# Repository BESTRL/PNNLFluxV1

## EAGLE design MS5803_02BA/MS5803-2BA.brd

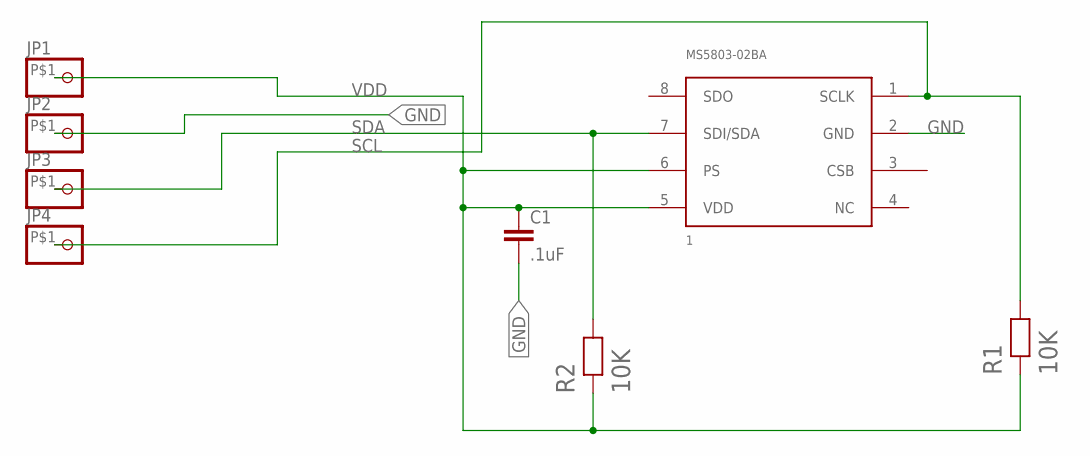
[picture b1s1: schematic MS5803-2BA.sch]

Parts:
C1: .1uF; C0805
JP1, JP2, JP3, JP4: PINHD-1X11X01SM; 1X01SM
MS5803-02BA: 1; MS5803-02BA
R1, R2: 10K; 2012(0805)RESISTOR

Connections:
GND: C1.2, JP2.P$1, MS5803-02BA.2 (GND)
SCL: JP4.P$1, MS5803-02BA.1 (SCLK), R1.2
SDA: JP3.P$1, MS5803-02BA.7 (SDI/SDA), R2.2
VDD: C1.1, JP1.P$1, MS5803-02BA.5 (VDD), MS5803-02BA.6 (PS), R1.1, R2.1

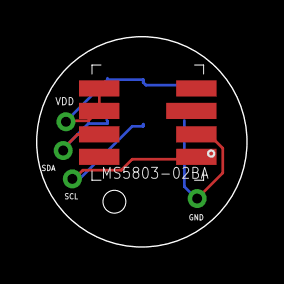
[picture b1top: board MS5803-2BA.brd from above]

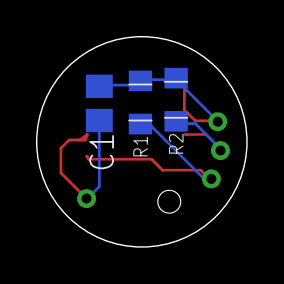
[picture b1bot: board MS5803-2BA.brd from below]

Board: 2 copper layers, 11.7 x 11.7 mm, 8 parts (3 on the bottom side), 4 nets.

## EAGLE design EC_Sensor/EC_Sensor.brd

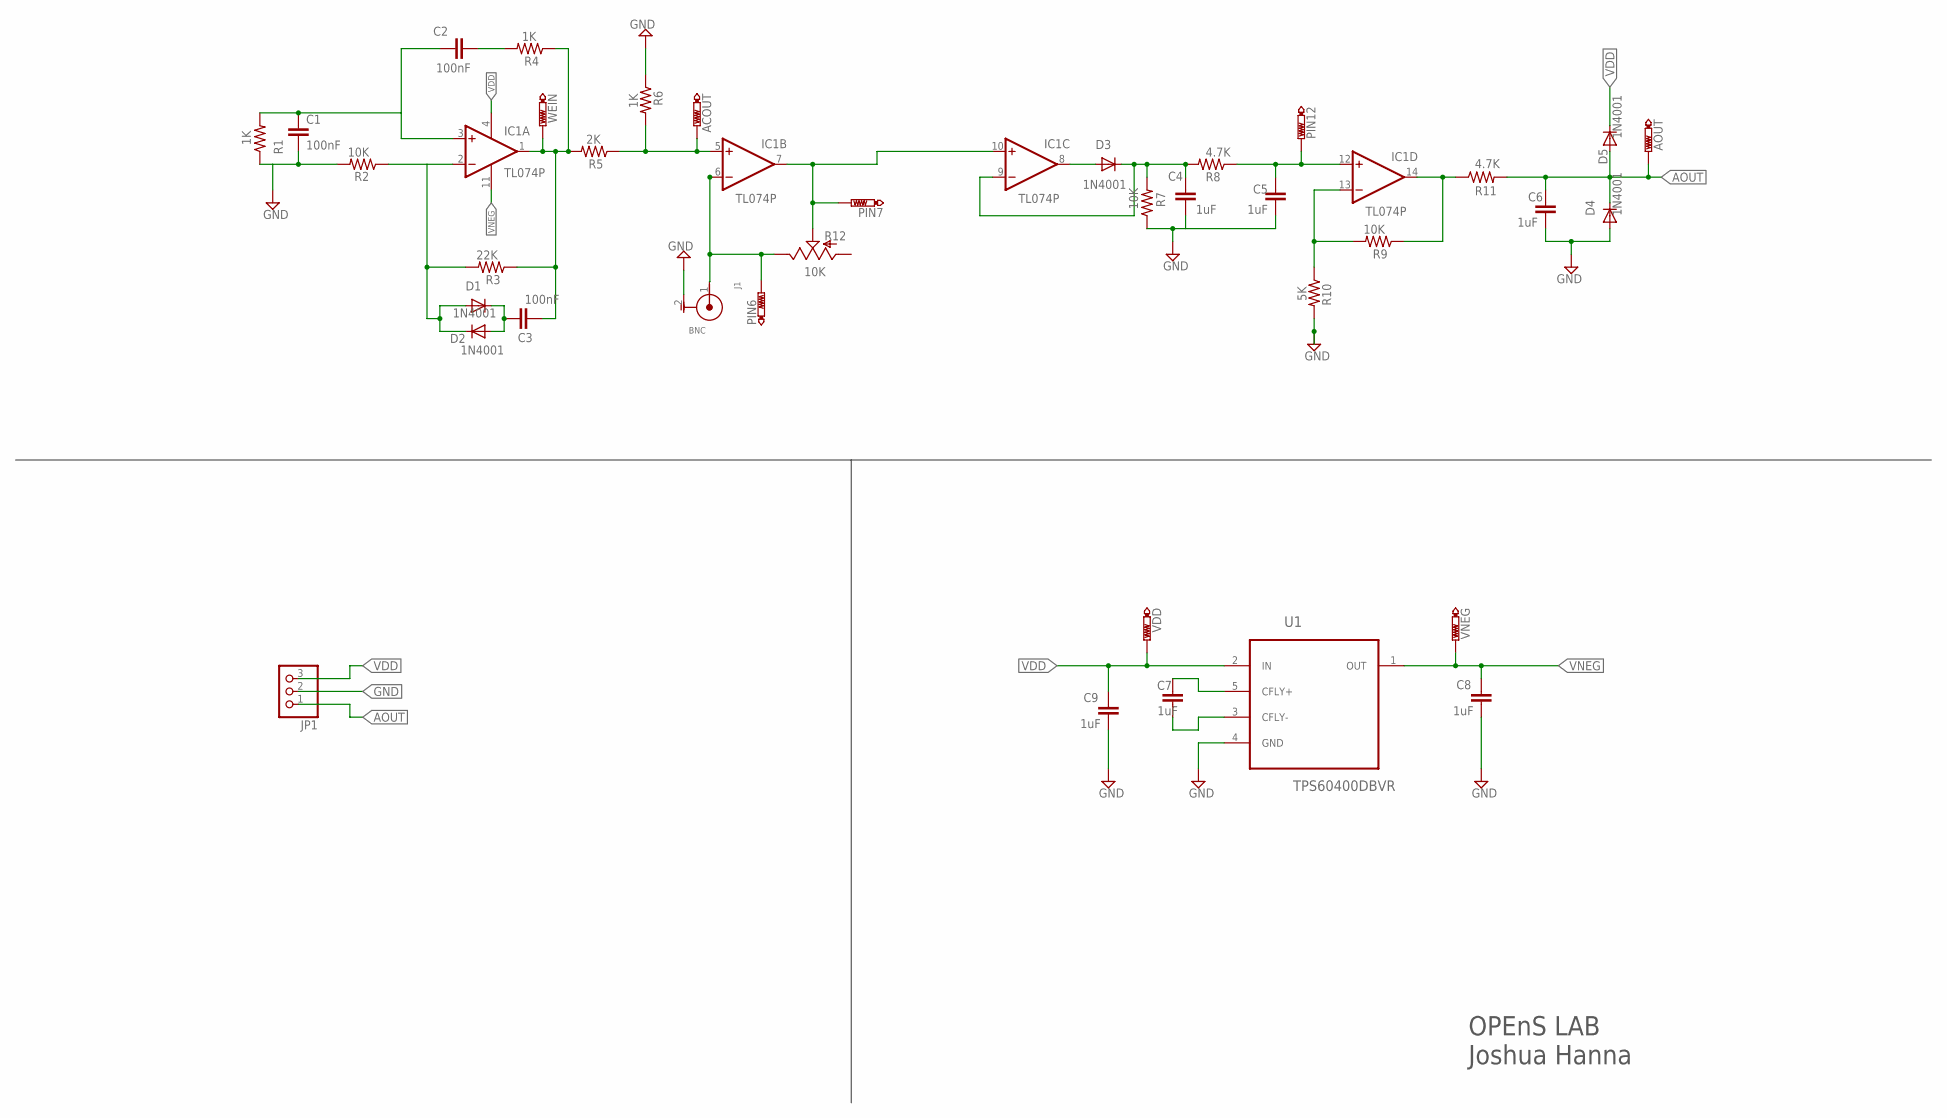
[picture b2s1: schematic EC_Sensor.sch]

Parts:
ACOUT: PTR1PAD1-13; P1-13
AOUT: PTR1PAD1-13; P1-13
C1, C2, C3: 100nF; C1206
C4, C5, C6, C7, C8, C9: 1uF; C1206
D1, D2, D3, D4, D5: 1N4001; D-5
IC1: TL074P; DIL14
J1: BNC; TE_227161-1
JP1: PINHD-1X3; 1X03
PIN6, PIN7, PIN12: PTR1PAD1-13; P1-13
R1, R4, R6: 1K; R1206
R2, R7, R9: 10K; R1206
R3: 22K; R1206
R5: 2K; R1206
R8, R11: 4.7K; R1206
R10: 5K; R1206
R12: 10K; B64Y
U1: TPS60400DBVR; SOT95P280X145-5N
VDD: PTR1PAD1-13; P1-13
VNEG: PTR1PAD1-13; P1-13
WEIN: PTR1PAD1-13; P1-13

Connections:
AOUT: AOUT.TP, C6.2, D4.C, D5.A, JP1.1, R11.2
GND: C1.2, C4.1, C5.1, C6.1, C8.1, C9.1, D4.A, J1.2 (G), JP1.2, R1.1, R2.2, R6.1, R7.1, R10.2, U1.4 (GND)
unnamed: C1.1, C2.1, IC1.3 (+IN), R1.2
unnamed: C2.2, R4.2
unnamed: C3.2, IC1.1 (OUT), R3.1, R4.1, R5.2, WEIN.TP
unnamed: D1.A, D2.C, IC1.2 (-IN), R2.1, R3.2
unnamed: ACOUT.TP, IC1.5 (+IN), R5.1, R6.2
unnamed: IC1.6 (-IN), J1.1 (C), PIN6.TP, R12.E
unnamed: C7.2, U1.5 (CFLY+)
unnamed: C3.1, D1.C, D2.A
unnamed: C4.2, D3.C, IC1.9 (-IN), R7.2, R8.2
unnamed: D3.A, IC1.8 (OUT)
unnamed: C7.1, U1.3 (CFLY-)
unnamed: C5.2, IC1.12 (+IN), PIN12.TP, R8.1
unnamed: IC1.13 (-IN), R9.2, R10.1
unnamed: IC1.14 (OUT), R9.1, R11.1
PIN7: IC1.7 (OUT), IC1.10 (+IN), PIN7.TP, R12.S
VDD: C9.2, D5.C, IC1.4 (V+), JP1.3, U1.2 (IN), VDD.TP
VNEG: C8.2, IC1.11 (V-), U1.1 (OUT), VNEG.TP

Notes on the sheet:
OPEnS LAB Joshua Hanna

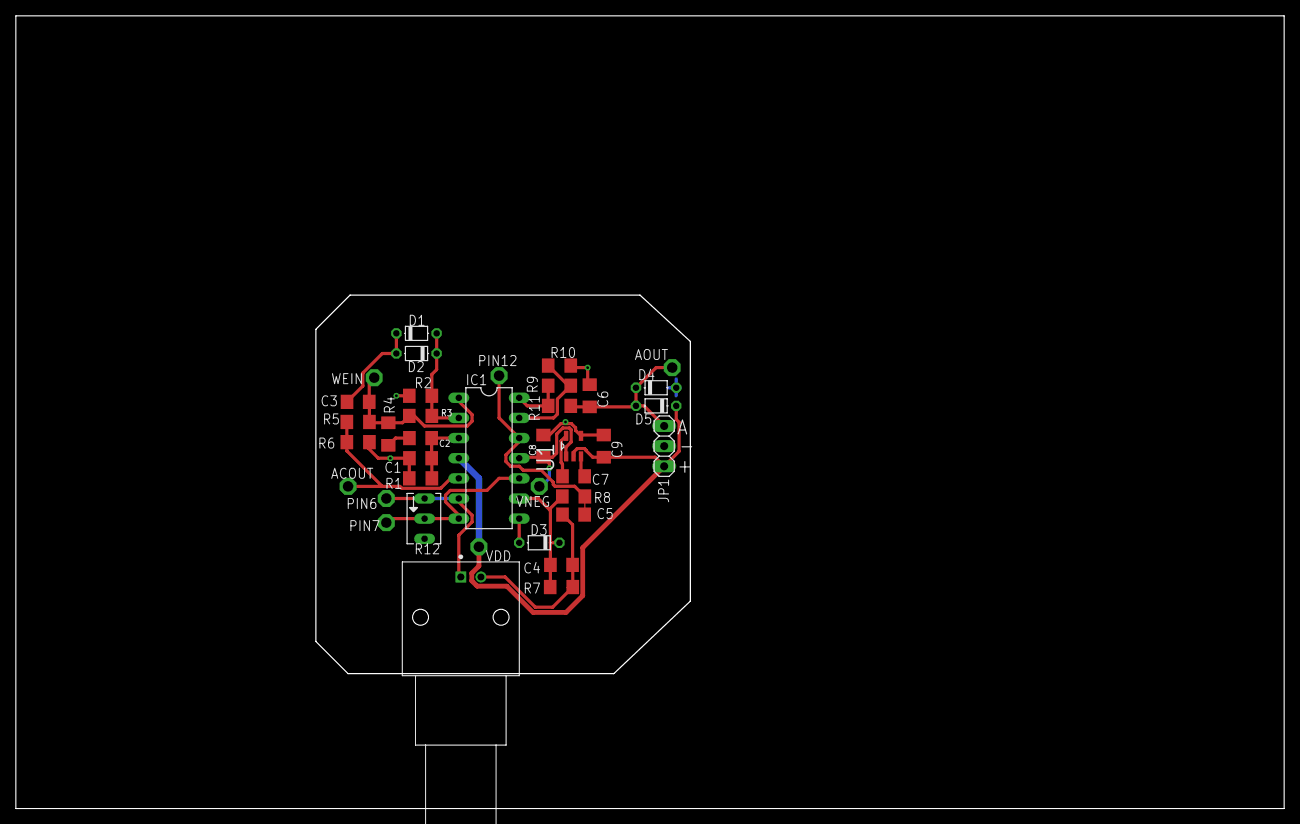
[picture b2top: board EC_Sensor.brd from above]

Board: 2 copper layers, 159.8 x 99.8 mm, 38 parts (0 on the bottom side), 19 nets.

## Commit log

2019-10-25 EC-Sensor push
2019-10-25 adding pressure/temp sensor
